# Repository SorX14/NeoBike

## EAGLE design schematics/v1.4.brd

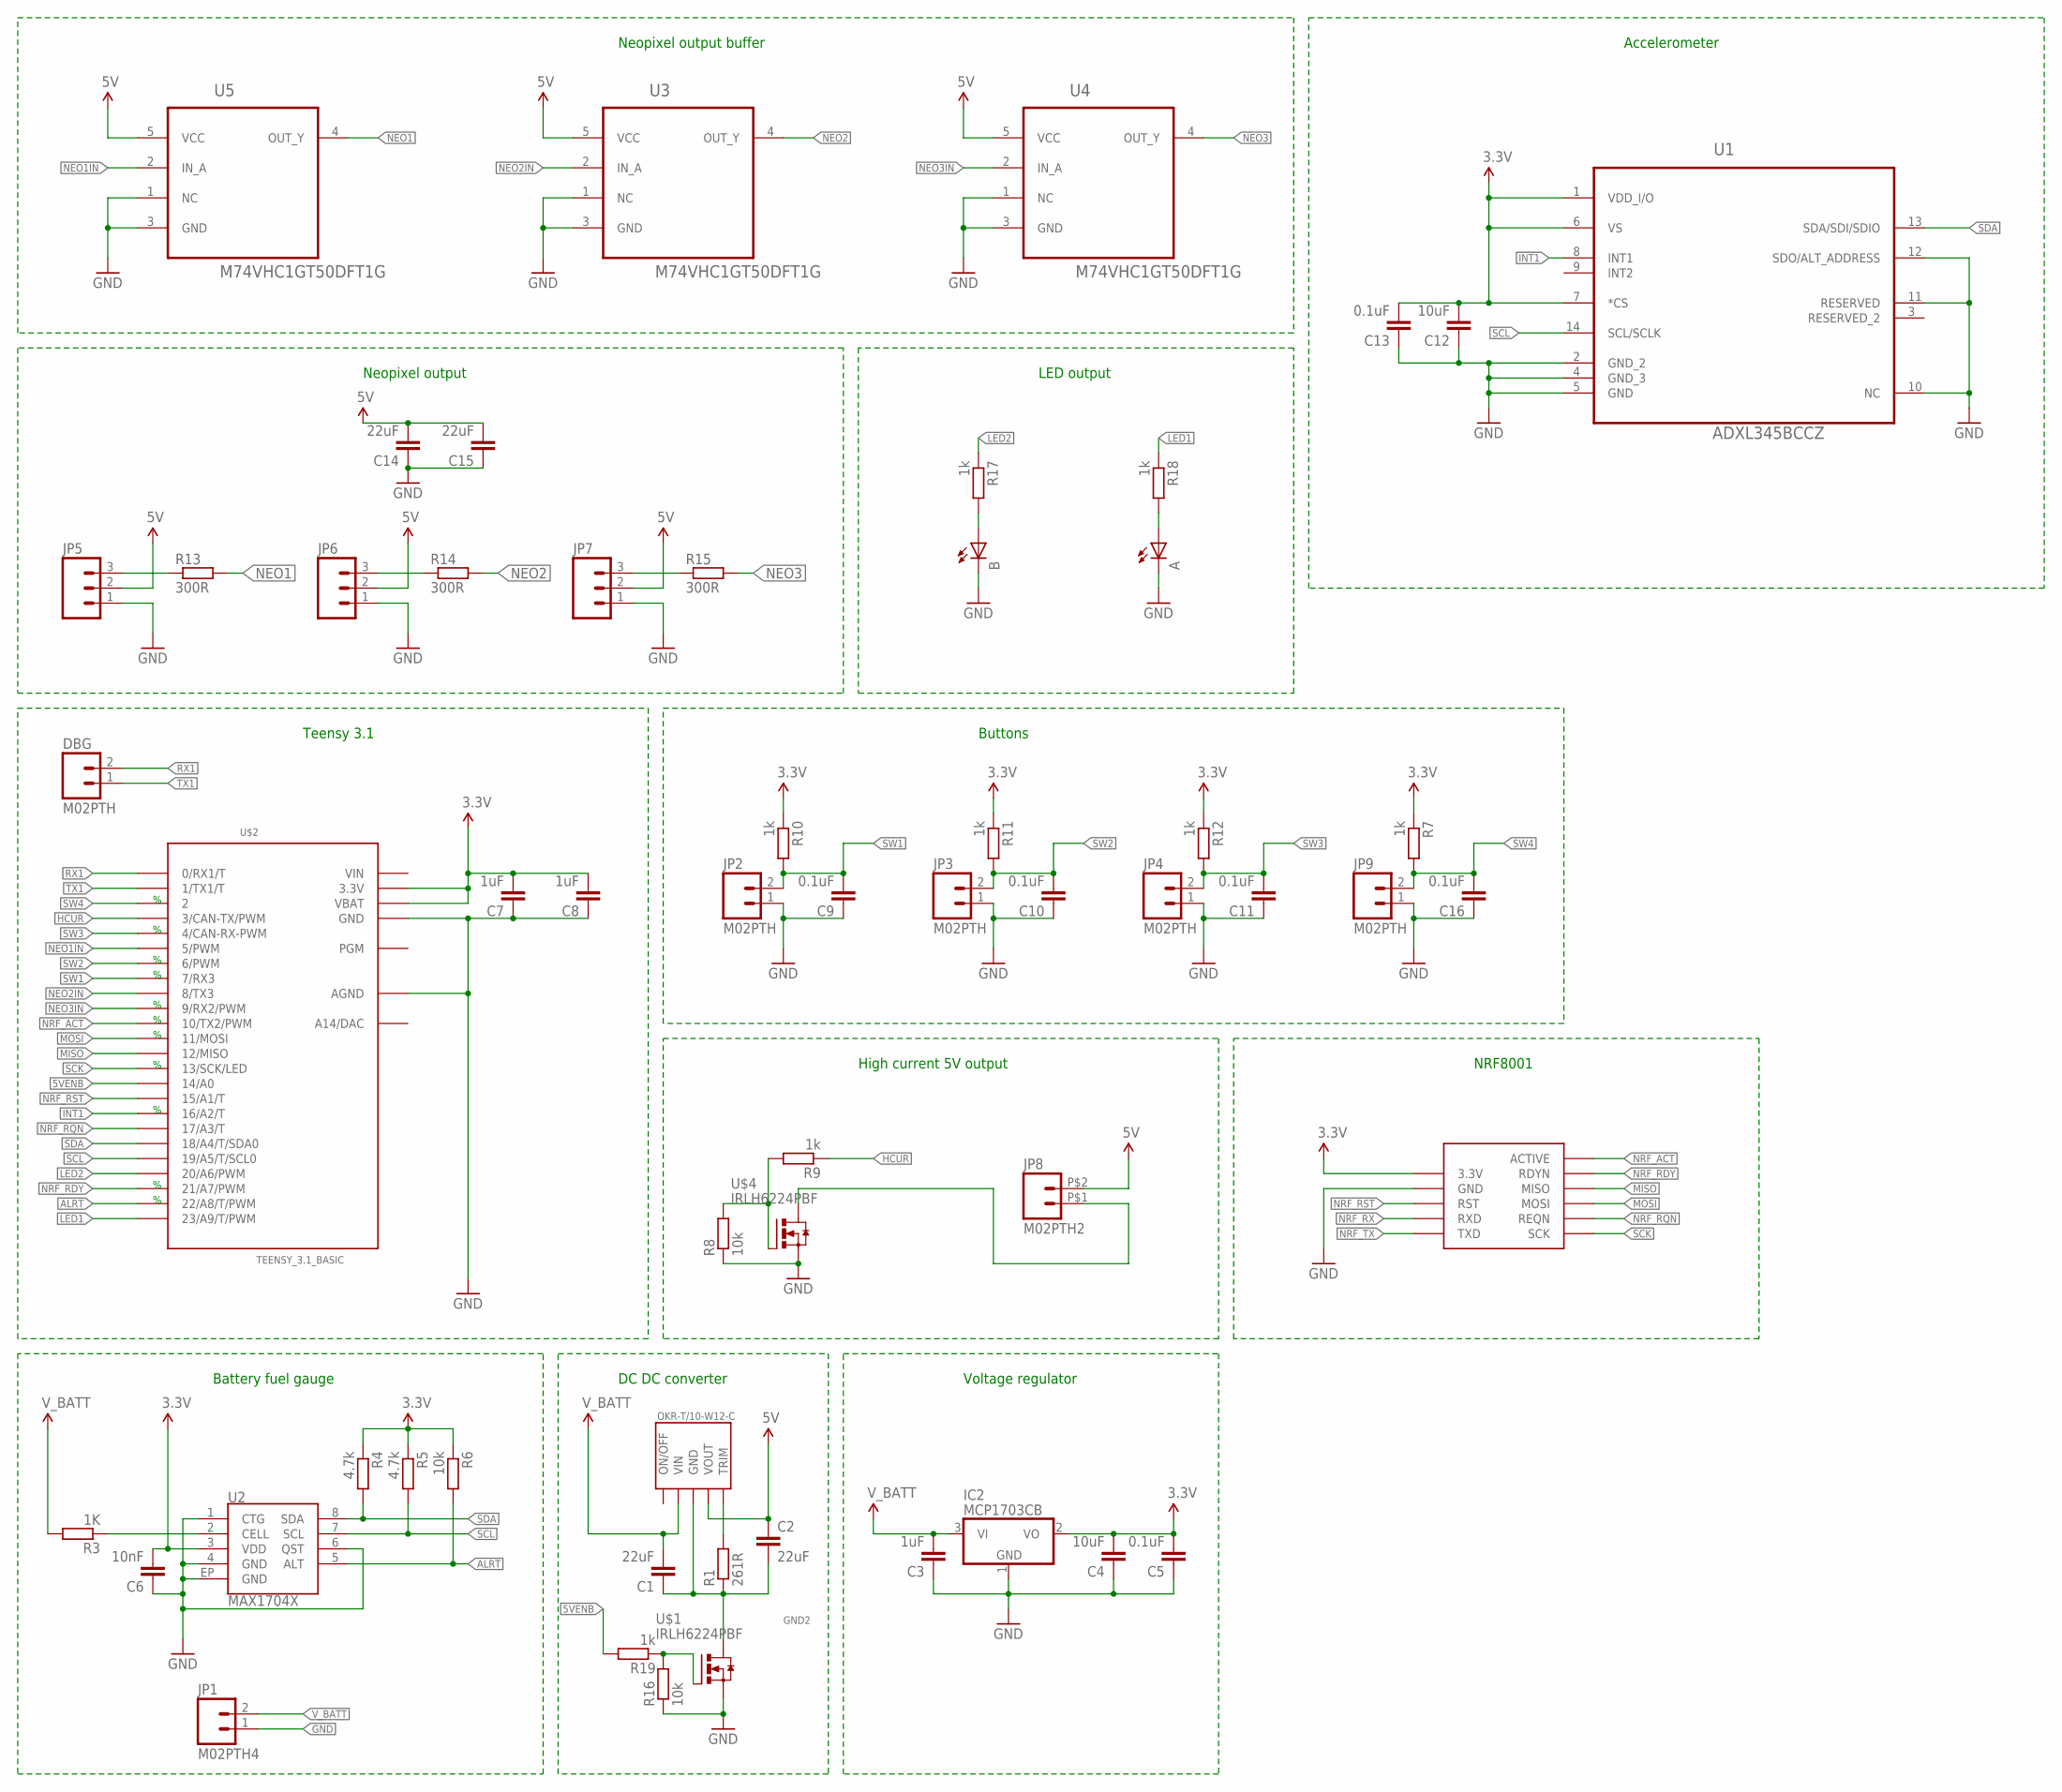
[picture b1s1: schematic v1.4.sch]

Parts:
A: LEDCHIPLED_0603; CHIPLED_0603
B: LEDCHIPLED_0603; CHIPLED_0603
C1, C2, C14, C15: 22uF; C0603
C3, C7, C8: 1uF; C0603
C4, C12: 10uF; C0603
C5, C9, C10, C11, C13, C16: 0.1uF; C0603
C6: 10nF; C0603
DBG: M02PTH; 1X02
IC2: MCP1703CB; SOT23
JP1: M02PTH4; 1X02_XTRA_BIG
JP2, JP3, JP4, JP9: M02PTH; 1X02
JP5, JP6, JP7: M03POLAR; MOLEX-1X3
JP8: M02PTH2; 1X02_BIG
OKR-T/10-W12-C: OKR-T/10C90
R1: 261R; R0603
R3: 1K; R0603
R4, R5: 4.7k; R0603
R6, R8, R16: 10k; R0603
R7, R9, R10, R11, R12, R17, R18, R19: 1k; R0603
R13, R14, R15: 300R; R0603
U1: ADXL345BCCZ; LGA14R80P3X6_300X500X100
U2: MAX1704X; TDFN-8
U3, U4, U5: M74VHC1GT50DFT1G; SOT65P210X110-5N
U$1, U$4: IRLH6224PBF; PQFN
U$2: TEENSY_3.1_BASIC
U$3: MOD-NRF8001

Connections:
3.3V: C4.2, C5.2, C6.2, C7.2, C8.2, C12.2, C13.2, IC2.2 (VO), R4.1, R5.1, R6.1, R7.1, R10.1, R11.1, R12.1, U1.1 (VDD_I/O), U1.6 (VS), U1.7 (*CS), U2.3 (VDD), U$2.3.3V, U$2.3.3V1 (3.3V), U$2.VBAT, U$3.3.3V
5V: C2.1, C14.2, C15.2, JP5.2, JP6.2, JP7.2, JP8.P$2 (2), OKR-T/10-W12-C.P$4 (VOUT), U3.5 (VCC), U4.5 (VCC), U5.5 (VCC)
5VENB: R19.2, U$2.14/A0
5VENB2: R16.2, R19.1, U$1.P$4 (G)
ALRT: R6.2, U2.5 (ALT), U$2.22/A8 (22/A8/T/PWM)
GND: A.C, B.C, C3.1, C4.1, C5.1, C6.1, C7.1, C8.1, C9.1, C10.1, C11.1, C12.1, C13.1, C16.1, IC2.1 (GND), JP1.1, JP2.1, JP3.1, JP4.1, JP9.1, R16.1, U1.2 (GND_2), U1.4 (GND_3), U1.5 (GND), U1.10 (NC), U1.11 (RESERVED), U1.12 (SDO/ALT_ADDRESS), U2.1 (CTG), U2.4 (GND), U2.6 (QST), U2.EP (GND), U$1.P$1 (S), U$1.P$2 (S), U$1.P$3 (S), U$2.AGND, U$2.GND, U$2.GND1 (GND), U$3.GND
GND2: C1.1, C2.2, C14.1, C15.1, JP5.1, JP6.1, JP7.1, OKR-T/10-W12-C.P$3 (GND), R1.1, R8.1, U3.1 (NC), U3.3 (GND), U4.1 (NC), U4.3 (GND), U5.1 (NC), U5.3 (GND), U$1.P$5 (D), U$4.P$1 (S), U$4.P$2 (S), U$4.P$3 (S)
HCUR: R9.1, U$2.3 (3/CAN-TX/PWM)
INT1: U1.8 (INT1), U$2.16/A2 (16/A2/T)
LED: JP8.P$1 (1), U$4.P$5 (D)
LED1: R18.1, U$2.23/A9 (23/A9/T/PWM)
LED2: R17.1, U$2.20/A6 (20/A6/PWM)
MISO: U$2.12 (12/MISO), U$3.MISO
MOSI: U$2.11 (11/MOSI), U$3.MOSI
unnamed: OKR-T/10-W12-C.P$5 (TRIM), R1.2
unnamed: R3.1, U2.2 (CELL)
unnamed: R8.2, R9.2, U$4.P$4 (G)
unnamed: JP5.3, R13.1
unnamed: JP6.3, R14.1
unnamed: JP7.3, R15.1
unnamed: B.A, R17.2
unnamed: A.A, R18.2
NEO1: R13.2, U5.4 (OUT_Y)
NEO1IN: U5.2 (IN_A), U$2.5 (5/PWM)
NEO2: R14.2, U3.4 (OUT_Y)
NEO2IN: U3.2 (IN_A), U$2.8 (8/TX3)
NEO3: R15.2, U4.4 (OUT_Y)
NEO3IN: U4.2 (IN_A), U$2.9 (9/RX2/PWM)
NRF_ACT: U$2.10 (10/TX2/PWM), U$3.ACTIVE
NRF_RDY: U$2.21/A7 (21/A7/PWM), U$3.RDYN
NRF_RQN: U$2.17/A3 (17/A3/T), U$3.REQN
NRF_RST: U$2.15/A1 (15/A1/T), U$3.RST
NRF_RX: U$3.RXD
NRF_TX: U$3.TXD
RX1: DBG.2, U$2.0 (0/RX1/T)
SCK: U$2.13 (13/SCK/LED), U$3.SCK
SCL: R5.2, U1.14 (SCL/SCLK), U2.7 (SCL), U$2.19/A5 (19/A5/T/SCL0)
SDA: R4.2, U1.13 (SDA/SDI/SDIO), U2.8 (SDA), U$2.18/A4 (18/A4/T/SDA0)
SW1: C9.2, JP2.2, R10.2, U$2.7 (7/RX3)
SW2: C10.2, JP3.2, R11.2, U$2.6 (6/PWM)
SW3: C11.2, JP4.2, R12.2, U$2.4 (4/CAN-RX-PWM)
SW4: C16.2, JP9.2, R7.2, U$2.2
TX1: DBG.1, U$2.1 (1/TX1/T)
VIN: U$2.VIN
V_BATT: C1.2, C3.2, IC2.3 (VI), JP1.2, OKR-T/10-W12-C.P$2 (VIN), R3.2

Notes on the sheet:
DC DC converter
Voltage regulator
Battery fuel gauge
High current 5V output
Buttons
Teensy 3.1
NRF8001
Neopixel output
LED output
Accelerometer
Neopixel output buffer

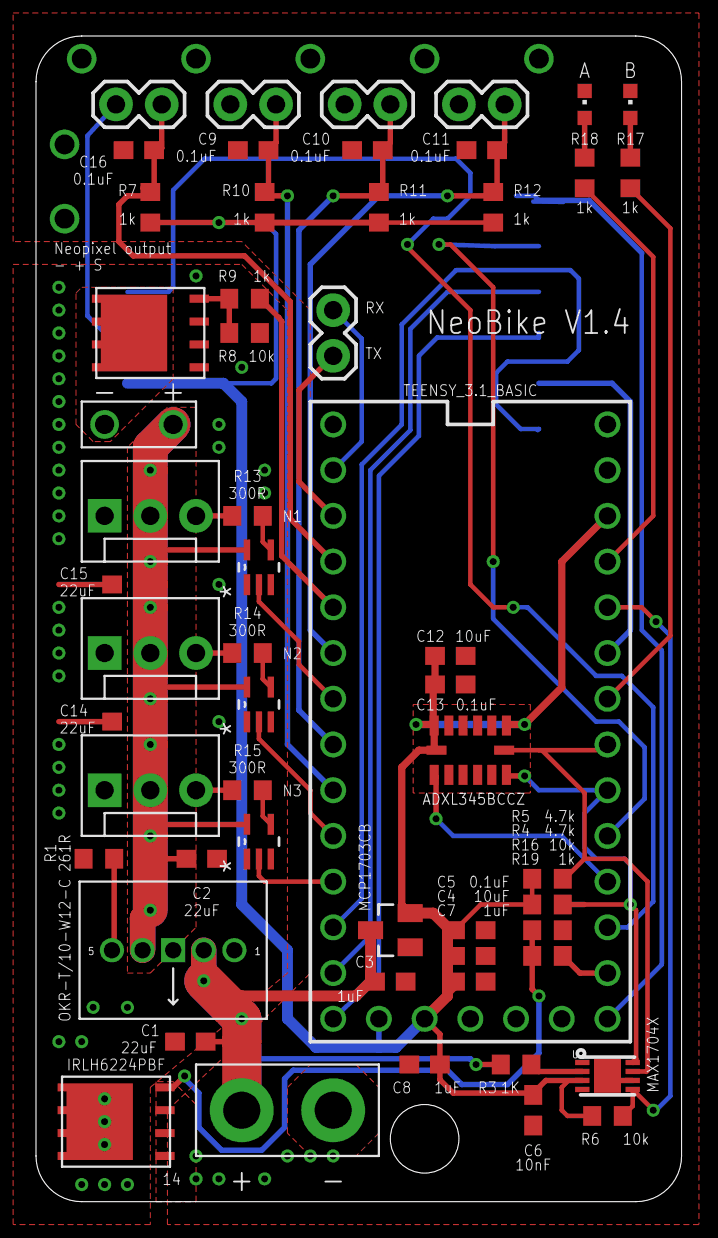
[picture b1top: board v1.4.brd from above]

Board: 2 copper layers, 35.9 x 64.8 mm, 57 parts (1 on the bottom side), 42 nets.

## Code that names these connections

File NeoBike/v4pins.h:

#ifndef neobikepins_h
#define neobikepins_h

// Teensy pins
// BTLE
#define NRF_RQN 17 		// 8
#define NRF_RDY 21		// 2
#define NRF_RST 15		// 9
#define NRF_ACT 10		// A3

// Accelerometer and voltage
#define ACC_ALRT 16		// 16
#define VCC_ALRT 22		// 5

// NeoPixel outputs and high current output
#define NEO1_PIN 9		// 5
#define NEO2_PIN 8		// 8
#define NEO3_PIN 5		// 9
#define HCUR 3			// 3

// Debug LEDs
#define LED1 23			// 17
#define LED2 20			// 15
#define LED3 0			// 13

// Enable 5V output
#define V5ENB 14		// 14

// Input switches
#define SW1 4
#define SW2 6
#define SW3 7
#define SW4 2

#define FRONT_LED_NUM 50
#define CENTER_LED_NUM 28
#define REAR_LED_NUM 60

#define FRONT_AVAILABLE_LED_NUM FRONT_LED_NUM / 2
#define CENTER_AVAILABLE_LED_NUM CENTER_LED_NUM
#define REAR_AVAILABLE_LED_NUM REAR_LED_NUM / 2

#define TOTAL_LED_NUM FRONT_LED_NUM + CENTER_LED_NUM + REAR_LED_NUM
#define TOTAL_AVAILABLE_LED_NUM (FRONT_LED_NUM / 2) + CENTER_LED_NUM + (REAR_LED_NUM / 2)

#endif

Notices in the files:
parts and their libraries:
SparkFun-Connectors: Licensing: CC v3.0 Share-Alike You are welcome to use this library for commercial purposes.
